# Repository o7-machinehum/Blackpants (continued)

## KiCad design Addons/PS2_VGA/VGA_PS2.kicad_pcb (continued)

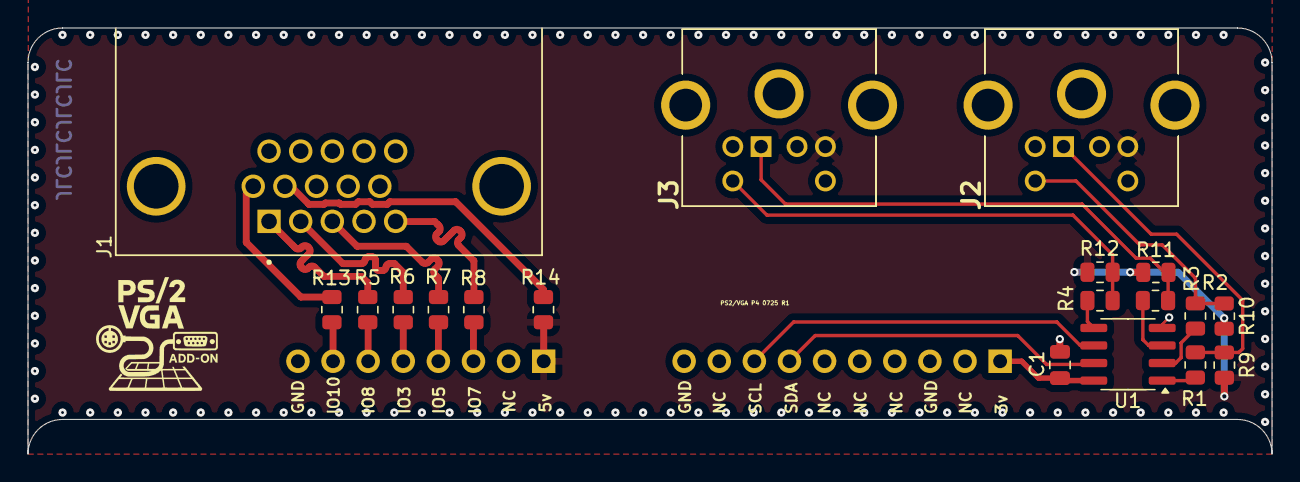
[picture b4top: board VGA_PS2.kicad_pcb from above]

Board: 2 copper layers, 90.0 x 30.8 mm, 21 parts (0 on the bottom side), 24 nets.

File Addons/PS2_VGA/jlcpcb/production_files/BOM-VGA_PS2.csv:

Comment,Designator,Footprint,LCSC,Quantity
220R,"R13,R8",R_0805_2012Metric,C114519,2
PCA9536D,U1,SOIC-8_3.9x4.9mm_P1.27mm,C129522,1
0R,,R_0805_2012Metric,C17477,0
330R,"R5,R6,R7",R_0805_2012Metric,C17630,3
200R,"R1,R2,R3,R4",R_0805_2012Metric,C2889551,4
5749266-1,"J2,J3",57492661,C3275792,2
100nF,C1,C_0805_2012Metric,C49678,1
L77HDE15SD1CH4FVGA,J1,AMPHENOL_L77HDE15SD1CH4FVGA,C5428609,1
10K,"R10,R11,R12,R9",R_0805_2012Metric,C84376,4
Conn_01x10_Pin,J4,PinHeader_1x10_P2.54mm_Horizontal,,1
Conn_01x08_Pin,J5,PinHeader_1x08_P2.54mm_Horizontal,,1

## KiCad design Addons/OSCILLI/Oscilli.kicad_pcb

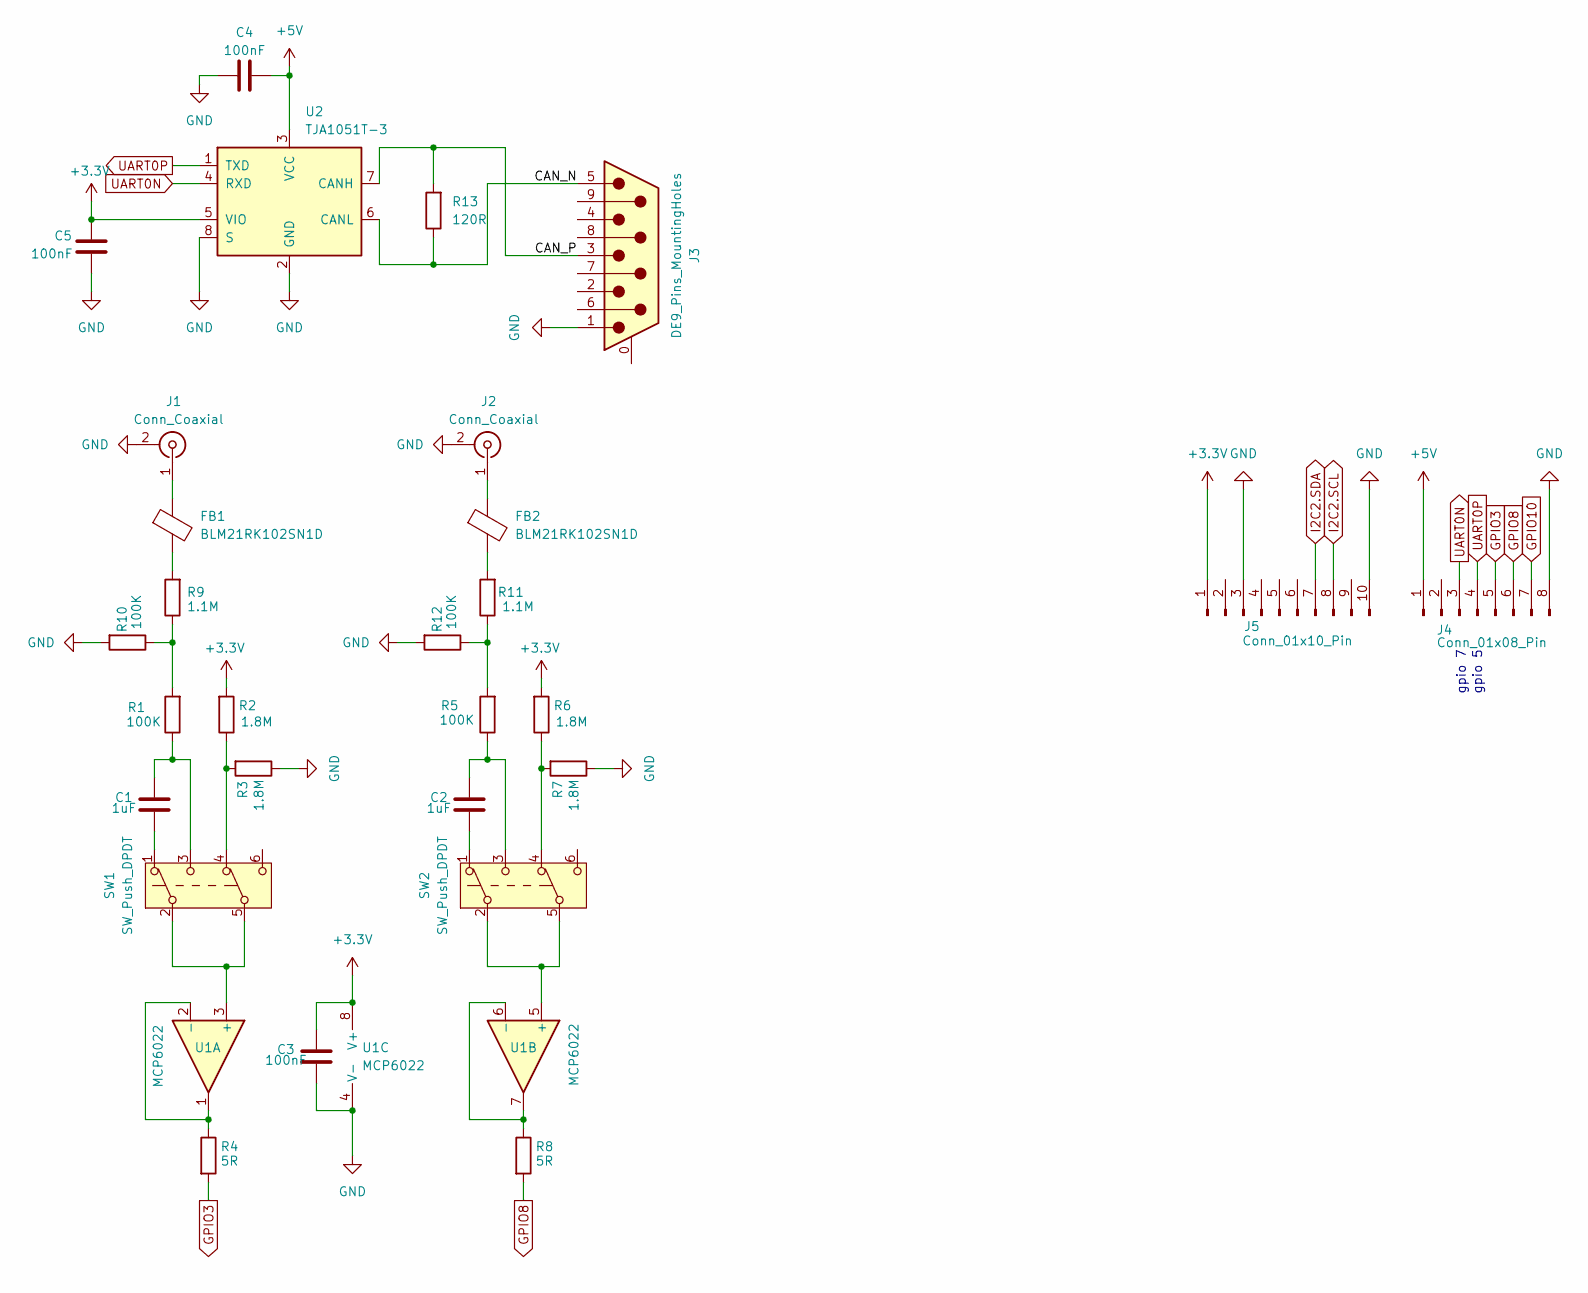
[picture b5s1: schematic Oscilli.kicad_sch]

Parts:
C1, C2: 1uF; C_0805_2012Metric
C3, C4, C5: 100nF; C_0805_2012Metric
FB1, FB2: BLM21RK102SN1D; L_0805_2012Metric
J1, J2: Conn_Coaxial; BNC_Amphenol_031-6575_Horizontal
J3: DE9_Pins_MountingHoles; DSUB-9_Socket_Horizontal_P2.77x2.84mm_EdgePinOffset4.94mm_H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
J4: Conn_01x08_Pin; PinHeader_1x08_P2.54mm_Horizontal
J5: Conn_01x10_Pin; PinHeader_1x10_P2.54mm_Horizontal
R1, R5, R10, R12: 100K; R_0805_2012Metric
R2, R3, R6, R7: 1.8M; R_0805_2012Metric
R4, R8: 5R; R_0805_2012Metric
R9, R11: 1.1M; R_0805_2012Metric
R13: 120R; R_0805_2012Metric
SW1, SW2: SW_Push_DPDT; SW_Push_2P2T_Toggle_CK_PVA2xxH4xxxxxxV2
U1: MCP6022; SOIC127P599X175-8N
U2: TJA1051T-3; SOIC-8_3.9x4.9mm_P1.27mm

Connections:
+3.3V: C3.2, C5.1, J5.1, R2.2, R6.2, U1.8 (V+), U2.5 (VIO)
+5V: C4.2, J4.1, U2.3 (VCC)
/CAN_N: J3.5, R13.1, U2.6 (CANL)
/CAN_P: J3.3, R13.2, U2.7 (CANH)
GND: C3.1, C4.1, C5.2, J1.2 (Ext), J2.2 (Ext), J3.1, J4.8, J5.3, J5.10, R3.1, R7.1, R10.2, R12.2, U1.4 (V-), U2.2 (GND), U2.8 (S)
GPIO3: J4.5, R4.2
GPIO8: J4.6, R8.2
GPIO10: J4.7
I2C2.SCL: J5.8
I2C2.SDA: J5.7
unnamed: C1.1, SW1.1 (A)
unnamed: C1.2, R1.1, SW1.3 (C)
unnamed: C2.1, SW2.1 (A)
unnamed: C2.2, R5.1, SW2.3 (C)
unnamed: FB1.2, R9.2
unnamed: FB2.2, R11.2
unnamed: FB1.1, J1.1 (In)
unnamed: FB2.1, J2.1 (In)
unnamed: R1.2, R9.1, R10.1
unnamed: R2.1, R3.2, SW1.4 (A)
unnamed: R6.1, R7.2, SW2.4 (A)
unnamed: R5.2, R11.1, R12.1
unnamed: SW1.2 (B), SW1.5 (B), U1.3 (+)
unnamed: R4.1, U1.1, U1.2 (-)
unnamed: SW2.2 (B), SW2.5 (B), U1.5 (+)
unnamed: R8.1, U1.6 (-), U1.7
UART0N: J4.3, U2.4 (RXD)
UART0P: J4.4, U2.1 (TXD)

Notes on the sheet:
gpio 7
gpio 5

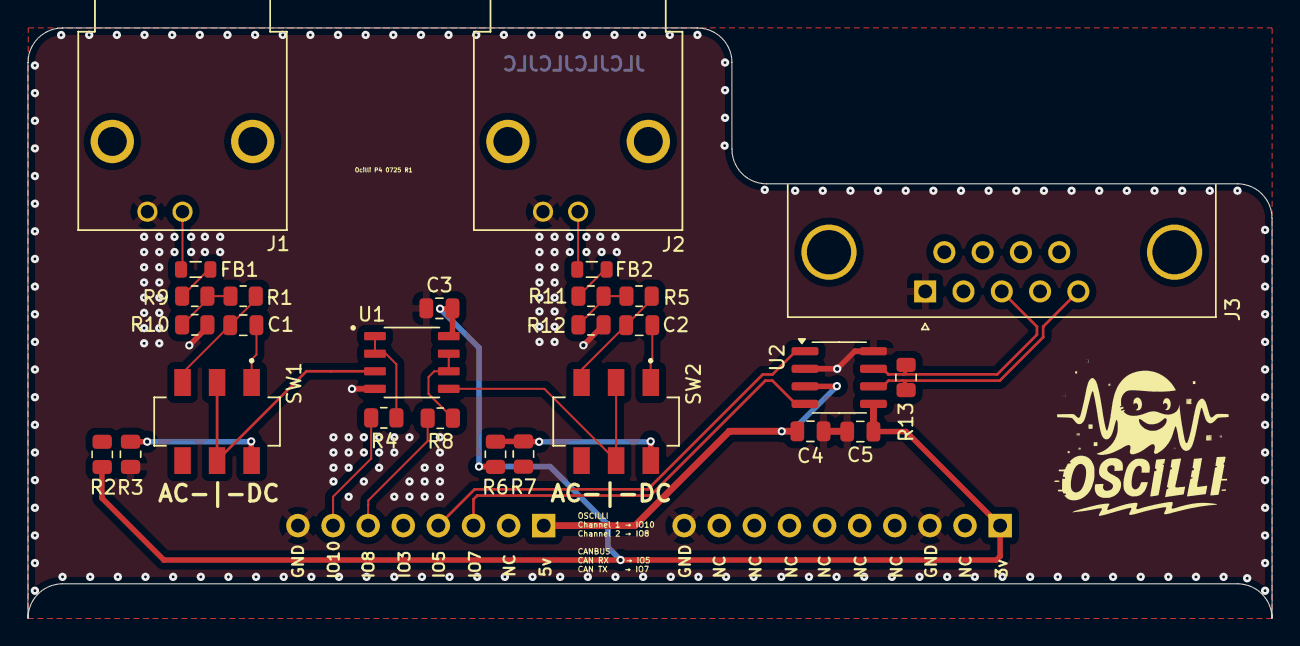
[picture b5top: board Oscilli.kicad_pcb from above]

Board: 2 copper layers, 90.0 x 42.7 mm, 29 parts (0 on the bottom side), 25 nets.

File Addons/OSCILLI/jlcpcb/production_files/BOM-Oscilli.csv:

Comment,Designator,Footprint,LCSC,Quantity
5R,"R4,R8",R_0805_2012Metric,C113035,2
100K,"R1,R10,R12,R5",R_0805_2012Metric,C149504,4
1.8M,"R2,R3,R6,R7",R_0805_2012Metric,C2930213,4
120R,R13,R_0805_2012Metric,C3013232,1
1.1M,"R11,R9",R_0805_2012Metric,C308358,2
1uF,"C1,C2",C_0805_2012Metric,C326587,2
TJA1051T-3,U2,SOIC-8_3.9x4.9mm_P1.27mm,C38695,1
100nF,"C3,C4,C5",C_0805_2012Metric,C49678,3
BLM21RK102SN1D,"FB1,FB2",L_0805_2012Metric,C498363,2
MCP6022,U1,SOIC127P599X175-8N,C57639,1
DE9_Pins_MountingHoles,J3,DSUB-9_Socket_Horizontal_P2.77x2.84mm_EdgePinOffset4.94mm_Housed_MountingHolesOffset4.94mm,,1
SW_Push_DPDT,SW2,SW_SLW-913535-2A-SMT,,1
Conn_01x10_Pin,J5,PinHeader_1x10_P2.54mm_Horizontal,,1
Conn_01x08_Pin,J4,PinHeader_1x08_P2.54mm_Horizontal,,1
Conn_Coaxial,J2,TE_5415218-5,,1
Conn_Coaxial,J1,TE_5415218-5,,1
SW_Push_DPDT,SW1,SW_SLW-913535-2A-SMT,,1

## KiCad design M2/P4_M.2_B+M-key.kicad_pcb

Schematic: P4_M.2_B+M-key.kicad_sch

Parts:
C2, C3, C4, C5, C6, C7, C9, C10, C11, C12, C14, C15, C16, C17, C18, C19, C20, C22, C23, C24, C25, C26, C27, C32, C38, C48, C50: 100nF; C_0201_0603Metric; LCSC C301918
C13, C21, C28, C29: 22pF; C_0201_0603Metric; LCSC C57783
C33, C34, C46, C47: 22uF; C_0603_1608Metric; LCSC C86295
C37, C49: 10uF; C_0603_1608Metric; LCSC C6119842
D1: LED; LED_0402_1005Metric; LCSC C22355736
D2: K24; D_SOD-123F; LCSC C5199107
D3: RED; LED_0603_1608Metric; LCSC C965799
IC1: XT25F128FWOIGT-W; WSON-8-1EP_6x5mm_P1.27mm_EP3.4x4mm; LCSC C3202839
IC2, IC4: TPS563202DRLR; SOT-563; LCSC C1513007
J1: Micro_SD_Card_Det2; uSD_CARD; LCSC C2962030
J2: USB_C_Receptacle_USB2.0_16P; USB_C_Receptacle_HRO_TYPE-C-31-M-22; LCSC C530612; not fitted
L1: VLS4012HBX-3R3M-N; IND_VLS4012HBX-3R3M-N; LCSC C3223566
L2: FTC252012S1R5MBCA; L_Changjiang_FNR252010S; LCSC C5832371
Q2: MMDT2222A; SOT-363_SC-70-6; LCSC C7603394
R1, R2: 5.1k; R_0201_0603Metric; LCSC C270344
R3, R4, R6, R7, R8, R24, R26, R30, R31: 10k; R_0201_0603Metric; LCSC C473048
R5: 4.7k; R_0201_0603Metric; LCSC C270346
R9: 220R; R_0201_0603Metric; LCSC C965330
R10, R11, R12, R13, R14: 51K; R_0201_0603Metric; LCSC C473471
R15: 1k; R_0201_0603Metric; LCSC C270365
R16, R23: 0; R_0201_0603Metric; LCSC C106228
R18: 47R; R_0201_0603Metric; LCSC C620443
R19: 100K; R_0201_0603Metric; LCSC C270364
R22: 31k; R_0201_0603Metric; LCSC C364366
R25: 4.9K; R_0201_0603Metric; LCSC C367640
R27: 150R; R_0201_0603Metric; LCSC C270329
R28, R29: 4.02k; R_0201_0603Metric; LCSC C270347
U2: ESP32-P4NRW16; IC_ESP32-P4NRW16; LCSC C22387510
U4: M.2-M-KEY
U5: CH340K; SSOP-10-1EP_3.9x4.9mm_P1mm_EP2.1x3.3mm; LCSC C968586
Y1: 32KHz; Crystal_SMD_3215-2Pin_3.2x1.5mm; LCSC C5361379
Y2: 40MHz; Crystal_SMD_2016-4Pin_2.0x1.6mm; LCSC C20885029

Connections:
/1.2V: C7.2, C20.2, C26.2, C33.1, C34.1, L2.1, R25.2, U2.26 (VDD_HP_0), U2.76 (VDD_HP_2), U2.91 (VDD_HP_3)
/3.3V: C2.2, C3.2, C5.2, C9.2, C10.2, C12.2, C14.2, C19.2, C22.2, C24.2, C25.2, C46.1, C47.1, C50.2, L1.1, R4.1, R5.1, R6.1, R7.1, R8.2, R15.1, R16.2, R22.2, U2.9 (VDDPST_1), U2.21 (VDDPST_2), U2.30 (VDDPST_3), U2.51 (VCCA), U2.59 (VDDPST), U2.62 (VDDPST_4), U2.67 (VDDPST), U2.75 (VDDPST_LDO), U2.77 (VDDPST_DCDC), U2.96 (VDDPST_6), U2.101 (VDDA), U4.68, U4.70, U4.72, U4.74, U5.7 (VCC), U5.10 (V3)
/CSI_CLKN: U2.45 (CSI_CLKN), U4.15
/CSI_CLKP: U2.44 (CSI_CLKP), U4.17
/CSI_DATAN0: U2.42 (CSI_DATAN0), U4.23
/CSI_DATAN1: U2.46 (CSI_DATAN1), U4.11
/CSI_DATAP0: U2.43 (CSI_DATAP0), U4.21
/CSI_DATAP1: U2.47 (CSI_DATAP1), U4.9
/CSI_REXT: R28.1, U2.48 (CSI_REXT)
/DSI_CLKN: U2.37 (DSI_CLKN), U4.35
/DSI_CLKP: U2.38 (DSI_CLKP), U4.33
/DSI_DATAN0: U2.40 (DSI_DATAN0), U4.27
/DSI_DATAN1: U2.36 (DSI_DATAN1), U4.39
/DSI_DATAP0: U2.39 (DSI_DATAP0), U4.29
/DSI_DATAP1: U2.35 (DSI_DATAP1), U4.41
/DSI_REXT: R29.1, U2.34 (DSI_REXT)
/DTR: Q2.1 (E1), R31.1, U5.4 (~DTR)
/EN_DCDC: IC2.5 (EN), U2.79 (EN_DCDC)
/EN_ESP: C6.2, Q2.3 (C2), R4.2, U2.103 (CHIP_PU)
/FB: IC4.6 (FB), R22.1, R24.2
/FB2: IC2.6 (FB), R23.1, R25.1, R26.2
/FLASH_CK: IC1.6 (SCLK), U2.32 (FLASH_CK)
/FLASH_CS: IC1.1 (CS#), R3.1, U2.27 (FLASH_CS)
/FLASH_D: IC1.5 (SI_(IO0)), U2.33 (FLASH_D)
/FLASH_HOLD: IC1.7 (HOLD#/_RESET#_(IO3)), U2.31 (FLASH_HOLD)
/FLASH_Q: IC1.2 (SO_(IO1)), U2.28 (FLASH_Q)
/FLASH_WP: IC1.3 (WP#_(IO2)), U2.29 (FLASH_WP)
/GPIO2: U2.2 (GPIO2), U4.22
/GPIO3: U2.3 (GPIO3), U4.58
/GPIO4: U2.4 (GPIO4), U4.24
/GPIO5: U2.5 (GPIO5), U4.56
/GPIO6: U2.6 (GPIO6), U4.26
/GPIO7: U2.7 (GPIO7), U4.54
/GPIO8: U2.8 (GPIO8), U4.28
/GPIO9: U2.10 (GPIO9), U4.52
/GPIO10: U2.11 (GPIO10), U4.30
/GPIO11: U2.12 (GPIO11)
/GPIO12: U2.13 (GPIO12), U4.32
/GPIO13: U2.14 (GPIO13), U4.34
/GPIO14: U2.15 (GPIO14), U4.36
/GPIO15: U2.16 (GPIO15), U4.38
/GPIO16: U2.17 (GPIO16), U4.40
/GPIO17: U2.18 (GPIO17), U4.42
/GPIO18: U2.19 (GPIO18), U4.46
/GPIO19: U2.20 (GPIO19), U4.44
/GPIO20: U2.22 (GPIO20), U4.48
/GPIO21: U2.23 (GPIO21)
/GPIO22: U2.24 (GPIO22), U4.50
/GPIO35: C11.2, Q2.6 (C1), R5.2, U2.66 (GPIO35)
/GPIO37: R6.2, U2.69 (GPIO37), U5.9 (RXD)
/GPIO38: R7.2, U2.70 (GPIO38), U5.8 (TXD)
/I2S_DATA: U2.52 (GPIO24), U4.2
/I2S_LRCK: U2.56 (GPIO27), U4.4
/I2S_MCLK: U2.55 (GPIO26), U4.6
/I2S_SCLK: U2.53 (GPIO25), U4.8
/REST_N: U2.92 (GPIO49)
/RTC: C23.2, R16.1, U2.102 (VBAT), U4.67
/RTS: Q2.4 (E2), R15.2, R30.1, U5.6 (~RTS)
/SD2_CLK: U2.63 (GPIO32), U4.18
/SD2_CMD: U2.64 (GPIO33), U4.20
/SD2_DATA0: U2.57 (GPIO28), U4.10
/SD2_DATA1: U2.61 (GPIO31), U4.12
/SD2_DATA2: U2.60 (GPIO30), U4.14
/SD2_DATA3: U2.58 (GPIO29), U4.16
/SD_CLK: R18.1, U2.84 (GPIO43)
/SD_CMD: J1.3 (CMD), R19.2, U2.86 (GPIO44)
/SD_DATA0: J1.7 (DAT0), R10.2, U2.80 (GPIO39)
/SD_DATA1: J1.8 (DAT1), R11.2, U2.81 (GPIO40)
/SD_DATA2: J1.1 (DAT2), R12.2, U2.82 (GPIO41)
/SD_DATA3: J1.2 (DAT3/CD), R13.2, U2.83 (GPIO42)
/SD_DET: J1.9 (DET_B), U2.88 (GPIO46)
/USB2HS_D+: U2.50 (DP), U4.3
/USB2HS_D-: U2.49 (DM), U4.5
/USB5V: C37.1, C49.1, D2.1 (K), IC2.1 (VIN), IC4.1 (VIN), IC4.5 (EN), R9.2, U4.69, U4.71, U4.73, U4.75
/USBJTAG_D+: J2.A6 (D+), J2.B6 (D+), U4.45, U5.1 (UD+)
/USBJTAG_D-: J2.A7 (D-), J2.B7 (D-), U4.47, U5.2 (UD-)
/VFLASH: C15.2, IC1.8 (VCC), R3.2, U2.71 (VFB1/VO1)
/VMIPI: C4.2, C17.2, U2.41 (VDD_MIPI_DPHY), U2.73 (VFB3/VO3)
/VPSRAM: C16.2, U2.72 (VFB2/VO2)
/V/SDMMC: C18.2, C27.2, C38.1, J1.4 (VDD), R10.1, R11.1, R12.1, R13.1, R14.1, R19.1, U2.74 (VFB4/VO4), U2.85 (VDDPST_5)
GND: C2.1, C3.1, C4.1, C5.1, C6.1, C7.1, C9.1, C10.1, C11.1, C12.1, C13.1, C14.1, C15.1, C16.1, C17.1, C18.1, C19.1, C20.1, C21.1, C22.1, C23.1, C24.1, C25.1, C26.1, C27.1, C28.2, C29.2, C33.2, C34.2, C37.2, C38.2, C46.2, C47.2, C49.2, C50.1, D1.1 (K), D3.1 (K), IC1.4 (VSS), IC1.9 (EP), IC2.3 (GND), IC4.3 (GND), J1.6 (VSS), J1.11 (SHIELD), J2.A1 (GND), J2.A12 (GND), J2.B1 (GND), J2.B12 (GND), J2.S1 (SHIELD), R1.2, R2.2, R24.1, R26.1, R28.2, R29.2, U2.105 (GND), U4.1, U4.7, U4.13, U4.19, U4.25, U4.31, U4.37, U4.43, U4.49, U4.MP (screw), U5.3 (GND), U5.11 (GND), Y2.2, Y2.4
unnamed: D1.2 (A), R27.2
unnamed: D2.2 (A), J2.A4 (VBUS), J2.A9 (VBUS), J2.B4 (VBUS), J2.B9 (VBUS)
unnamed: D3.2 (A), R9.1
unnamed: C32.2, IC2.4 (BST)
unnamed: C32.1, IC2.2 (SW), L2.2
unnamed: C48.2, IC4.4 (BST)
unnamed: C48.1, IC4.2 (SW), L1.2
unnamed: J1.5 (CLK), R18.2
unnamed: J1.10 (DET_A), R14.2
unnamed: J2.A5 (CC1), R1.1
unnamed: J2.B5 (CC2), R2.1
unnamed: Q2.2 (B1), R30.2
unnamed: Q2.5 (B2), R31.2
unnamed: R23.2, U2.78 (FB_DCDC)
unnamed: C21.2, U2.104 (GPIO0), Y1.2
unnamed: C13.2, U2.1 (GPIO1), Y1.1
unnamed: R8.1, U2.68 (GPIO36)
unnamed: R27.1, U2.94 (GPIO51)
unnamed: C29.1, U2.99 (XTAL_N), Y2.3
unnamed: C28.1, U2.100 (XTAL_P), Y2.1

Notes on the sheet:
40Mhz
UART / AUTO FLASHER
32Mhz
M.2 B+M KEY
FLASH
PD MAIN
1.8v 0.1A OUTPUT
2.5v 0.1A OUTPUT
POWER
1.8v / 3.3v 0.2A OUTPUT (SDIO)
ESP-P4

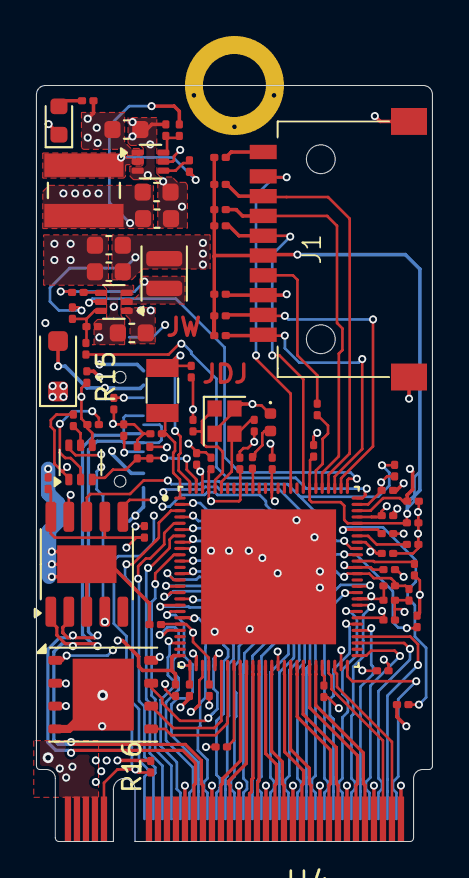
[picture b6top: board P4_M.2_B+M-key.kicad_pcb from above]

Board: 4 copper layers, 22.0 x 42.0 mm, 81 parts (1 on the bottom side), 98 nets.

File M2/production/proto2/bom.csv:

Comment,Designator,Footprint,LCSC
22pF,"C13,C21,C28,C29",Capacitor_SMD:C_0201_0603Metric,C57783
51K,"R10,R11,R12,R13,R14",Resistor_SMD:R_0201_0603Metric,C473471
RED,D3,LED_SMD:LED_0603_1608Metric,C965799
100nF,"C2,C3,C4,C5,C6,C7,C9,C10,C11,C12,C14,C15,C16,C17,C18,C19,C20,C22,C23,C24,C25,C26,C27,C32,C38,C48,C50",Capacitor_SMD:C_0201_0603Metric,C301918
4.02k,"R28,R29",Resistor_SMD:R_0201_0603Metric,C270347
MMDT2222A,Q2,Package_TO_SOT_SMD:SOT-363_SC-70-6,C7603394
4.7k,R5,Resistor_SMD:R_0201_0603Metric,C270346
ESP32-P4NRW16,U2,P4_M.2_B+M-key:IC_ESP32-P4NRW16,C22387510
10k,"R3,R4,R6,R7,R8,R24,R26,R30,R31",Resistor_SMD:R_0201_0603Metric,C473048
4.9K,R25,Resistor_SMD:R_0201_0603Metric,C367640
40MHz,Y2,Crystal:Crystal_SMD_2016-4Pin_2.0x1.6mm,C20885029
100K,R19,Resistor_SMD:R_0201_0603Metric,C270364
LED,D1,LED_SMD:LED_0402_1005Metric,C22355736
22uF,"C33,C34,C46,C47",Capacitor_SMD:C_0603_1608Metric,C86295
10uF,"C37,C49",Capacitor_SMD:C_0603_1608Metric,C6119842
TPS563202DRLR,"IC2,IC4",Package_TO_SOT_SMD:SOT-563,C1513007
5.1k,"R1,R2",Resistor_SMD:R_0201_0603Metric,C270344
XT25F128FWOIGT-W,IC1,Package_SON:WSON-8-1EP_6x5mm_P1.27mm_EP3.4x4mm,C3202839
K24,D2,Diode_SMD:D_SOD-123F,C5199107
31k,R22,Resistor_SMD:R_0201_0603Metric,C364366
32KHz,Y1,Crystal:Crystal_SMD_3215-2Pin_3.2x1.5mm,C5361379
0,R23,Resistor_SMD:R_0201_0603Metric,C106228
Micro_SD_Card_Det2,J1,WHY:uSD_CARD,C2962030
47R,R18,Resistor_SMD:R_0201_0603Metric,C620443
FTC252012S1R5MBCA,L2,Inductor_SMD:L_Changjiang_FNR252010S,C5832371
VLS4012HBX-3R3M-N,L1,P4_M.2_B+M-key:IND_VLS4012HBX-3R3M-N,C3223566
CH340K,U5,Package_SO:SSOP-10-1EP_3.9x4.9mm_P1mm_EP2.1x3.3mm,C968586
150R,R27,Resistor_SMD:R_0201_0603Metric,C270329
220R,R9,Resistor_SMD:R_0201_0603Metric,C965330

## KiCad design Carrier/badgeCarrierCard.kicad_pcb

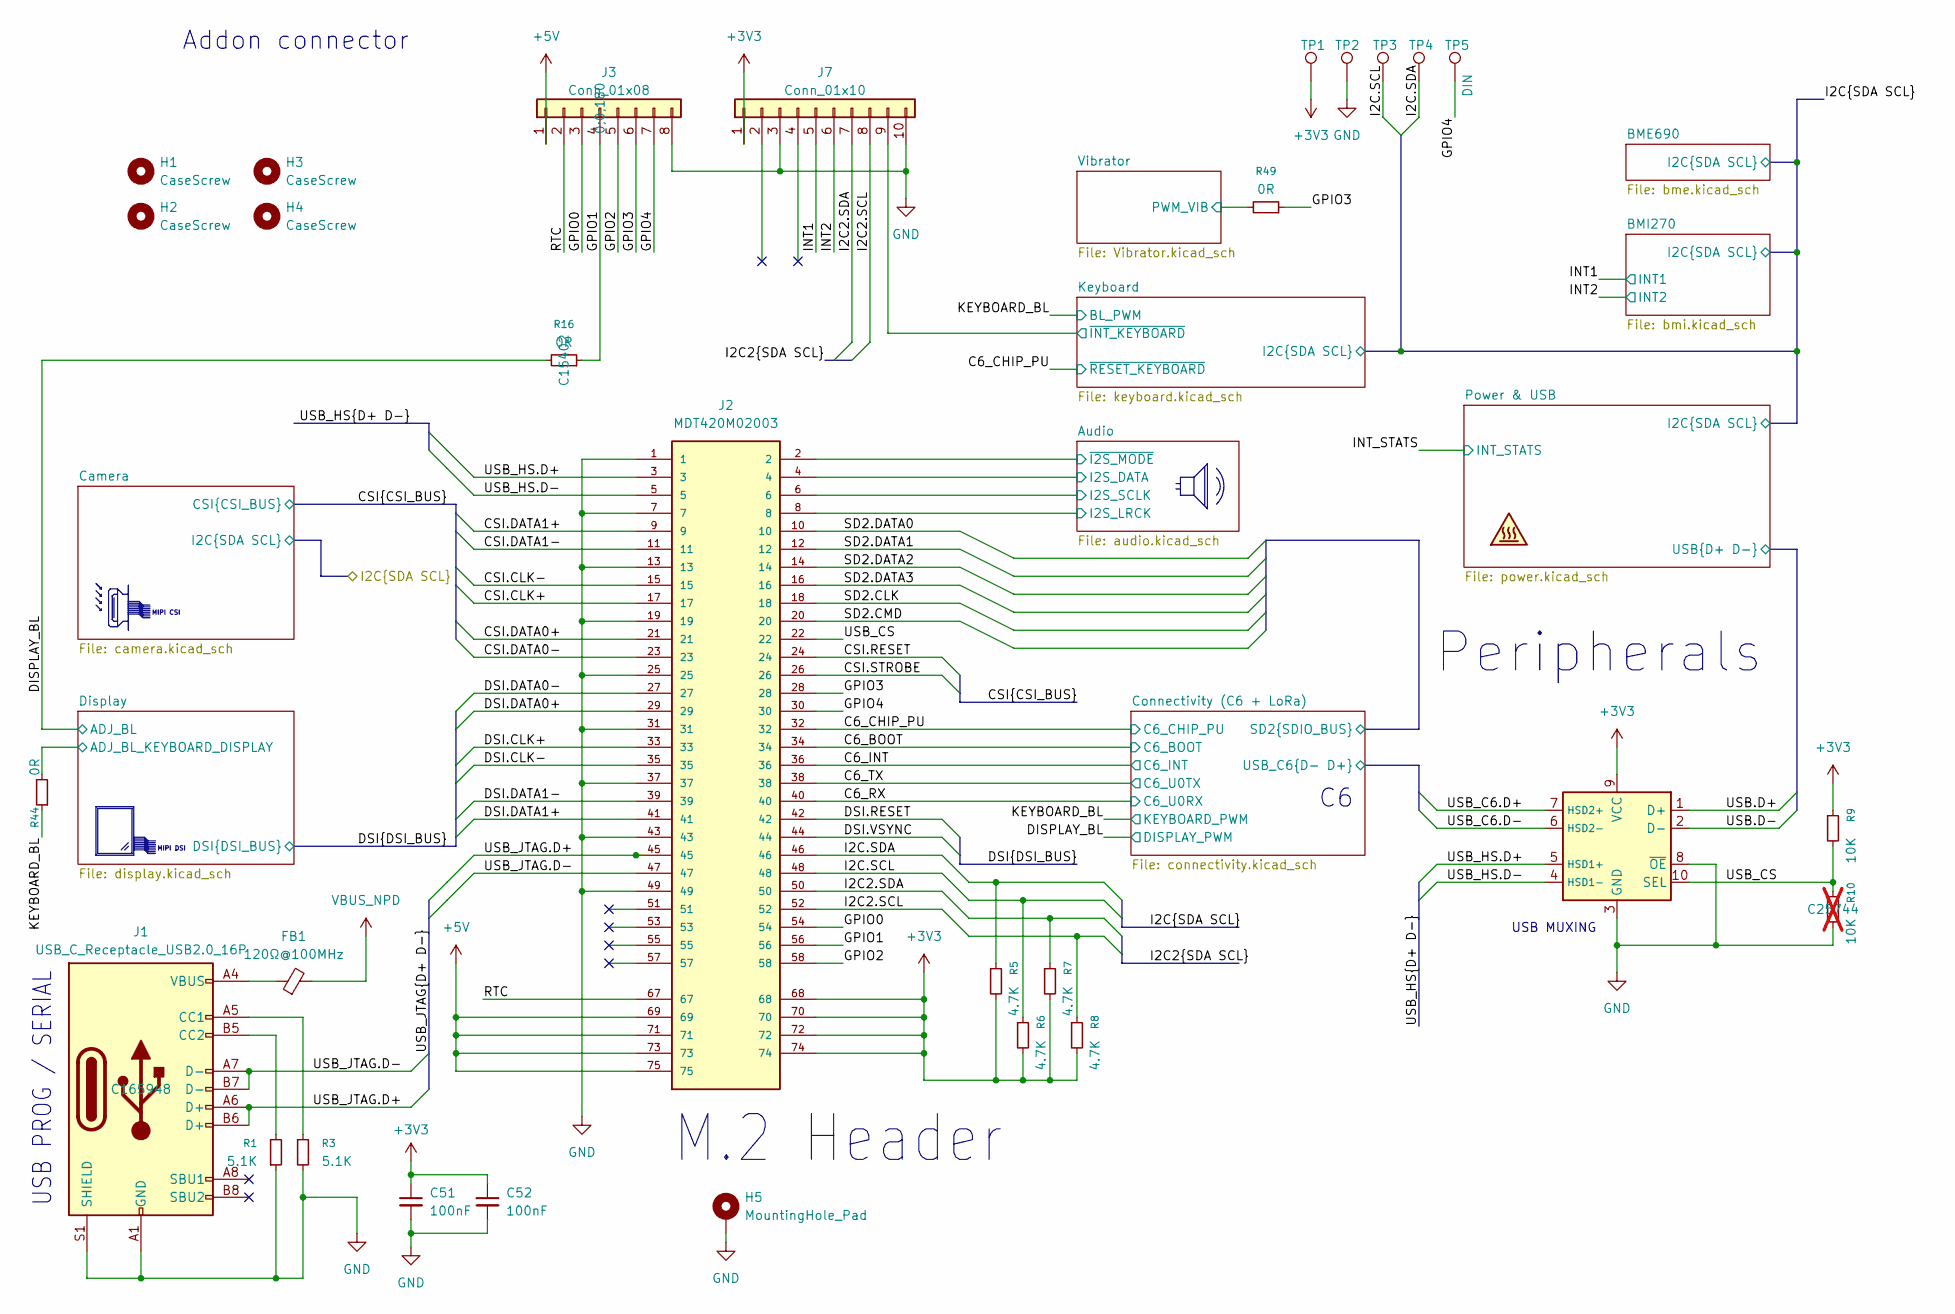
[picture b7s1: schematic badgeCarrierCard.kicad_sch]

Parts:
C51, C52: 100nF; C_0402_1005Metric; LCSC C307331
FB1: 120Ω@100MHz; L_0402_1005Metric; LCSC C76891
H1, H2, H3, H4: CaseScrew; MountingHole_2.2mm_M2
H5: MountingHole_Pad; Standoff; LCSC C19626599
J1: USB_C_Receptacle_USB2.0_16P; USB_C_Receptacle_HRO_TYPE-C-31-M-12; LCSC C165948
J2: MDT420M02003; AMPHENOL_MDT420M02003; PARTREV 1; LCSC C410529
J3: Conn_01x08; SMD_8; LCSC C5142241
J7: Conn_01x10; SMD_10; LCSC C5142243
R1, R3: 5.1K; R_0402_1005Metric; LCSC C25905
R5, R6, R7, R8: 4.7K; R_0402_1005Metric; LCSC C25900
R9: 10K; R_0402_1005Metric; LCSC C25744
R10: 10K; R_0402_1005Metric; LCSC C25744; not fitted
R16, R44: 0R; R_0603_1608Metric; LCSC C15402
R49: 0R; R_0402_1005Metric; LCSC C15402
TP1, TP2, TP3, TP4: TestPoint; TestPoint_Pad_D1.0mm
TP5: DIN; TestPoint_Pad_D1.0mm
U11: TPSGM7227YUWQ10G; UQFN-10_1.4x1.8mm_P0.4mm; LCSC C42379165

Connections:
/Audio/I2S_DATA: J2.4; also elsewhere on the board
/Audio/I2S_LRCK: J2.8; also elsewhere on the board
/Audio/I2S_SCLK: J2.6; also elsewhere on the board
/Audio/~I2S_MODE: J2.2; also elsewhere on the board
/C6_BOOT: J2.34; also elsewhere on the board
/C6_CHIP_PU: J2.32; also elsewhere on the board
/C6_INT: J2.36; also elsewhere on the board
/C6_RX: J2.40; also elsewhere on the board
/C6_TX: J2.38; also elsewhere on the board
/CSI.CLK+: J2.17; also elsewhere on the board
/CSI.CLK-: J2.15; also elsewhere on the board
/CSI.DATA0+: J2.21; also elsewhere on the board
/CSI.DATA0-: J2.23; also elsewhere on the board
/CSI.DATA1+: J2.9; also elsewhere on the board
/CSI.DATA1-: J2.11; also elsewhere on the board
/CSI.RESET: J2.24; also elsewhere on the board
/CSI.STROBE: J2.26; also elsewhere on the board
/Connectivity (C6 + LoRa)/SD2.CLK: J2.18; also elsewhere on the board
/Connectivity (C6 + LoRa)/SD2.CMD: J2.20; also elsewhere on the board
/Connectivity (C6 + LoRa)/SD2.DATA0: J2.10; also elsewhere on the board
/Connectivity (C6 + LoRa)/SD2.DATA1: J2.12; also elsewhere on the board
/Connectivity (C6 + LoRa)/SD2.DATA2: J2.14; also elsewhere on the board
/Connectivity (C6 + LoRa)/SD2.DATA3: J2.16; also elsewhere on the board
/Connectivity (C6 + LoRa)/USB_C6.D+: U11.7 (HSD2+); also elsewhere on the board
/Connectivity (C6 + LoRa)/USB_C6.D-: U11.6 (HSD2-); also elsewhere on the board
/DISPLAY_BL: R16.2; also elsewhere on the board
/DSI.CLK+: J2.33; also elsewhere on the board
/DSI.CLK-: J2.35; also elsewhere on the board
/DSI.DATA0+: J2.29; also elsewhere on the board
/DSI.DATA0-: J2.27; also elsewhere on the board
/DSI.DATA1+: J2.41; also elsewhere on the board
/DSI.DATA1-: J2.39; also elsewhere on the board
/DSI.RESET: J2.42; also elsewhere on the board
/DSI.VSYNC: J2.44
/Display/ADJ_BL_KEYBOARD_DISPLAY: R44.2; also elsewhere on the board
/GPIO0: J2.54, J3.3
/GPIO1: J2.56, J3.4, R16.1
/GPIO2: J2.58, J3.5
/GPIO3: J2.28, J3.6, R49.1
/GPIO4: J2.30, J3.7, TP5.1
/I2C2.SCL: J2.52, J7.8, R8.1
/I2C2.SDA: J2.50, J7.7, R7.1
/I2C.SCL: J2.48, R6.1, TP3.1; also elsewhere on the board
/I2C.SDA: J2.46, R5.1, TP4.1; also elsewhere on the board
/INT1: J7.5; also elsewhere on the board
/INT2: J7.6; also elsewhere on the board
/KEYBOARD_BL: R44.1; also elsewhere on the board
/Keyboard/~INT_KEYBOARD: J7.9; also elsewhere on the board
/Power & USB/USB.D+: U11.1 (D+); also elsewhere on the board
/Power & USB/USB.D-: U11.2 (D-); also elsewhere on the board
/RTC: J2.67, J3.2
/USB_CS: J2.22, R9.2, R10.1, U11.10 (SEL)
/USB_HS.D+: J2.3, U11.5 (HSD1+)
/USB_HS.D-: J2.5, U11.4 (HSD1-)
/USB_JTAG.D+: J1.A6 (D+), J1.B6 (D+), J2.45
/USB_JTAG.D-: J1.A7 (D-), J1.B7 (D-), J2.47
unnamed: FB1.1, J1.A4 (VBUS), J1.A9 (VBUS), J1.B4 (VBUS), J1.B9 (VBUS)
unnamed: J1.A5 (CC1), R3.1
unnamed: J1.B5 (CC2), R1.2
VBUS_NPD: FB1.2; also elsewhere on the board

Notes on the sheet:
M.2 Header
MIPI CSI
Peripherals
USB MUXING
USB PROG / SERIAL
MIPI DSI
Addon connector

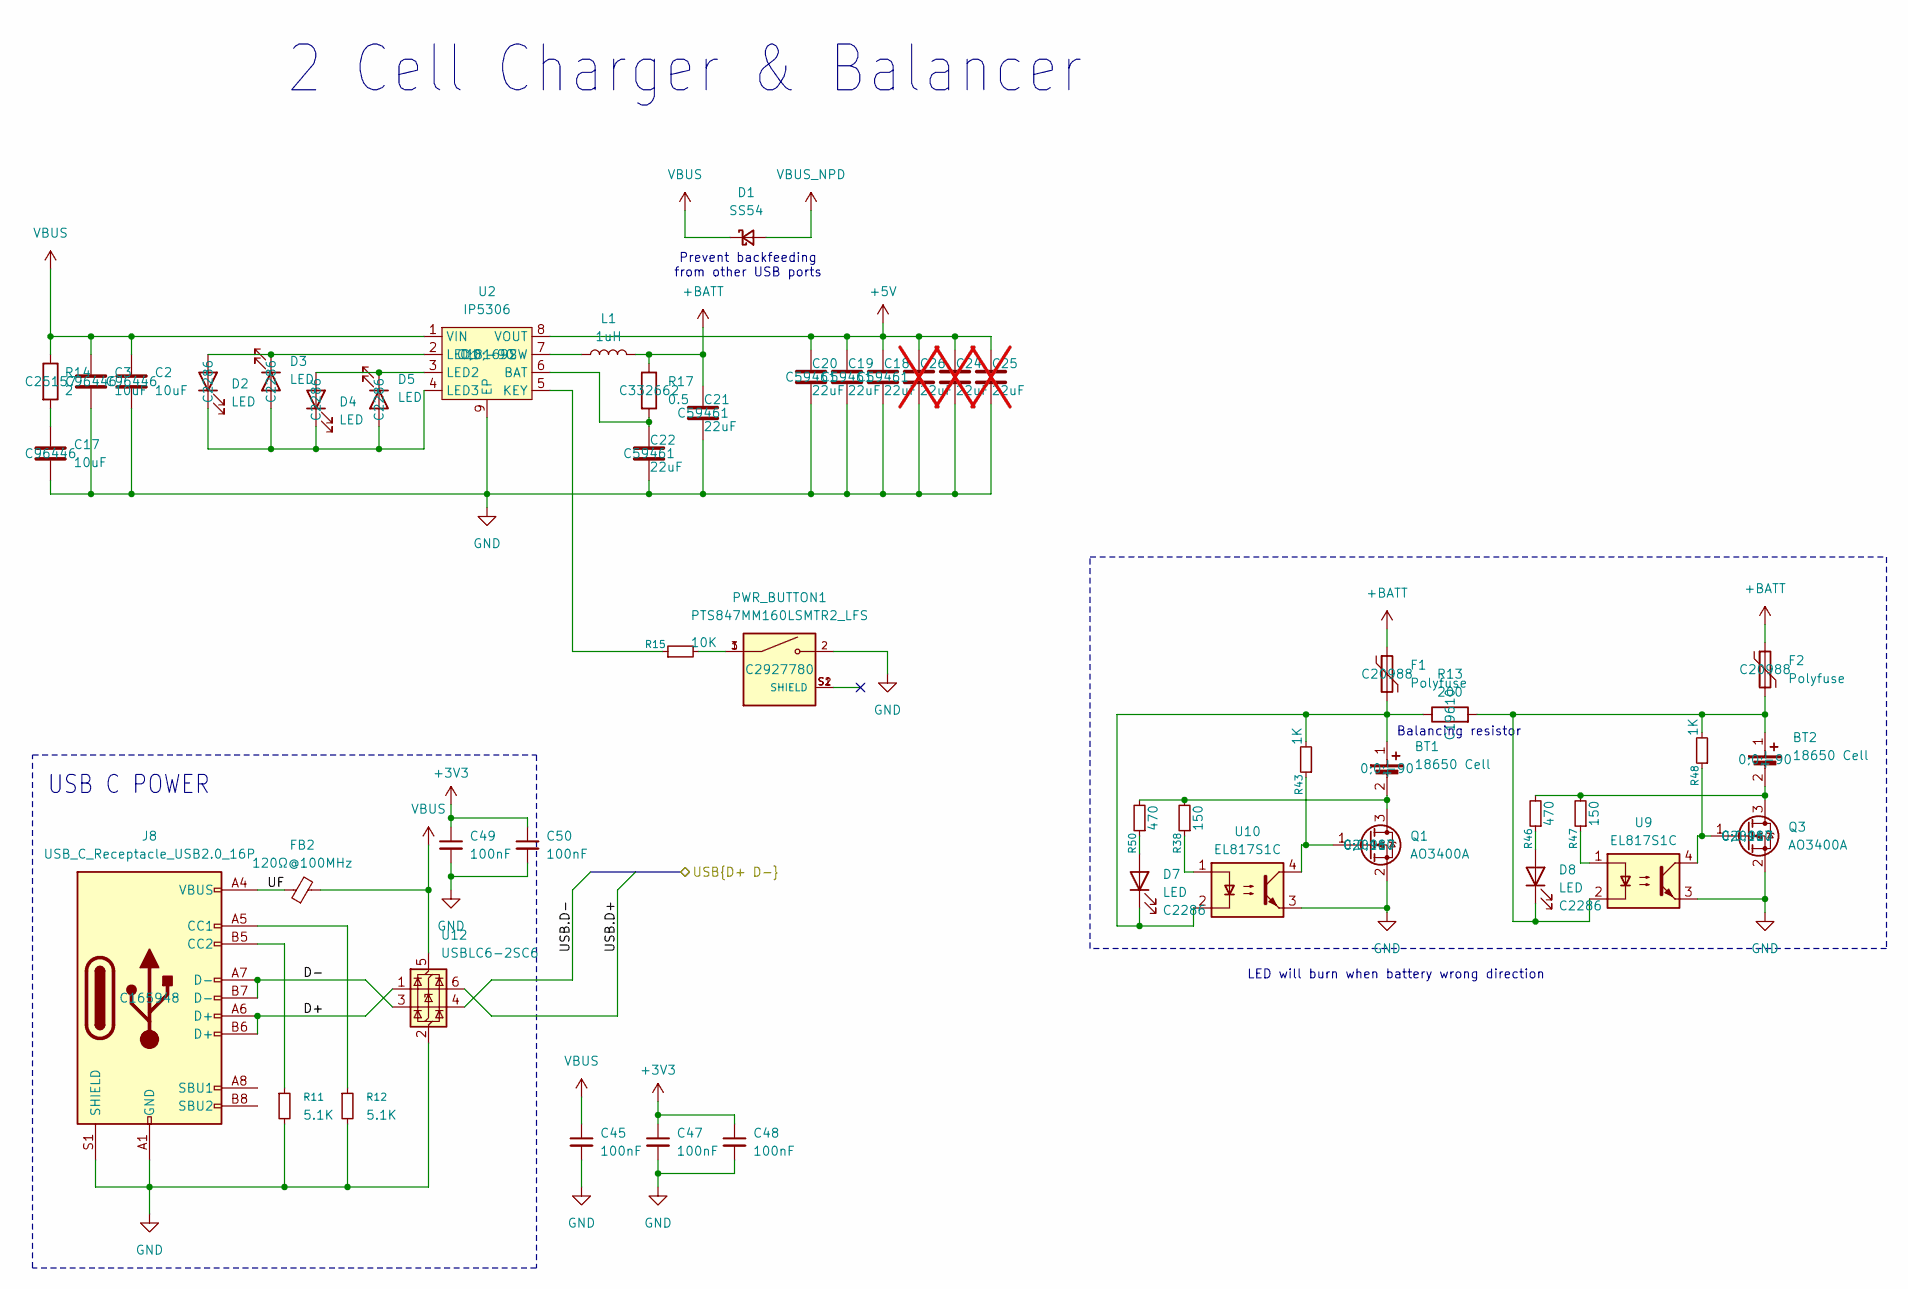
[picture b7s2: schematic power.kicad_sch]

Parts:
BT1, BT2: 18650 Cell; BH-18650-B1BA002; LCSC C2988620
C2, C3, C17: 10uF; C_0603_1608Metric; LCSC C96446
C18, C19, C20, C21, C22: 22uF; C_0603_1608Metric; LCSC C59461
C24, C25, C26: 22uF; C_0603_1608Metric; LCSC C59461; not fitted
C45, C47, C48, C49, C50: 100nF; C_0402_1005Metric; LCSC C307331
D1: SS54; D_SMA; LCSC C22452
D2, D3, D4, D5: LED; D_0603_1608Metric; LCSC C2286
D7, D8: LED; LED_0603_1608Metric; LCSC C2286
F1, F2: Polyfuse; Fuse_1206_3216Metric; LCSC C20988
FB2: 120Ω@100MHz; L_0402_1005Metric; LCSC C76891
J8: USB_C_Receptacle_USB2.0_16P; USB_C_Receptacle_HRO_TYPE-C-31-M-12; LCSC C165948
L1: 1uH; L_Changjiang_FXL0420; LCSC C32712969
PWR_BUTTON1: PTS847MM160LSMTR2_LFS; SW_PTS847MM160LSMTR2_LFS; PARTREV B; LCSC C2927780
Q1, Q3: AO3400A; SOT-23; LCSC C20917
R11, R12: 5.1K; R_0402_1005Metric; LCSC C25905
R13: 200; R_2010_5025Metric; LCSC C19610
R14: 2; R_0402_1005Metric; LCSC C25157
R15: 10K; R_0402_1005Metric; LCSC C25744
R17: 0.5; R_0402_1005Metric; LCSC C332662
R38, R47: 150; R_0402_1005Metric; LCSC C25082
R43, R48: 1K; R_0402_1005Metric; LCSC C11702
R46, R50: 470; R_0402_1005Metric; LCSC C25117
U2: IP5306; HSOP-8-1EP_3.9x4.9mm_P1.27mm_EP2.41x3.1mm_ThermalVias; LCSC C181692
U9, U10: EL817S1C; SOIC254P1030X390-4N; LCSC C2912100
U12: USBLC6-2SC6; SOT-23-6; LCSC C7519

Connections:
+BATT: C21.1, F1.1, F2.1, L1.2, R17.1
/Power & USB/D+: J8.A6 (D+), J8.B6 (D+), U12.1 (I/O1)
/Power & USB/D-: J8.A7 (D-), J8.B7 (D-), U12.3 (I/O2)
/Power & USB/UF: FB2.1, J8.A4 (VBUS), J8.A9 (VBUS), J8.B4 (VBUS), J8.B9 (VBUS)
/Power & USB/USB.D+: U12.6 (I/O1); also elsewhere on the board
/Power & USB/USB.D-: U12.4 (I/O2); also elsewhere on the board
unnamed 92: BT1.1 (+), D7.1 (K), F1.2, R13.1, R43.2, U10.2; also elsewhere on the board
unnamed 93: BT1.2 (-), Q1.3 (D), R38.2, R50.2; also elsewhere on the board
unnamed: BT2.1 (+), D8.1 (K), F2.2, R13.2, R48.2, U9.2
unnamed: BT2.2 (-), Q3.3 (D), R46.2, R47.2
unnamed: C17.1, R14.2
unnamed: D2.2 (A), D3.1 (K), U2.2 (LED1)
unnamed: D2.1 (K), D3.2 (A), D4.1 (K), D5.2 (A), U2.4 (LED3)
unnamed: D4.2 (A), D5.1 (K), U2.3 (LED2)
unnamed: D8.2 (A), R46.1
unnamed: J8.A5 (CC1), R12.1
unnamed: J8.B5 (CC2), R11.1
unnamed: PWR_BUTTON1.1, PWR_BUTTON1.3, R15.2
unnamed 119: Q1.1 (G), R43.1, U10.4; also elsewhere on the board
unnamed: Q3.1 (G), R48.1, U9.4
unnamed 122: R38.1, U10.1; also elsewhere on the board
unnamed: R47.1, U9.1
unnamed: C22.1, R17.2, U2.6 (BAT)
unnamed: R15.1, U2.5 (KEY)
unnamed: L1.1, U2.7 (SW)
VBUS: C2.1, C3.1, C45.1, D1.1 (K), FB2.2, R14.1, U2.1 (VIN), U12.5 (VBUS)
VBUS_NPD: D1.2 (A); also elsewhere on the board

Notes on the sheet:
2 Cell Charger & Balancer
Balancing resistor
Prevent backfeeding from other USB ports
LED will burn when battery wrong direction
USB C POWER

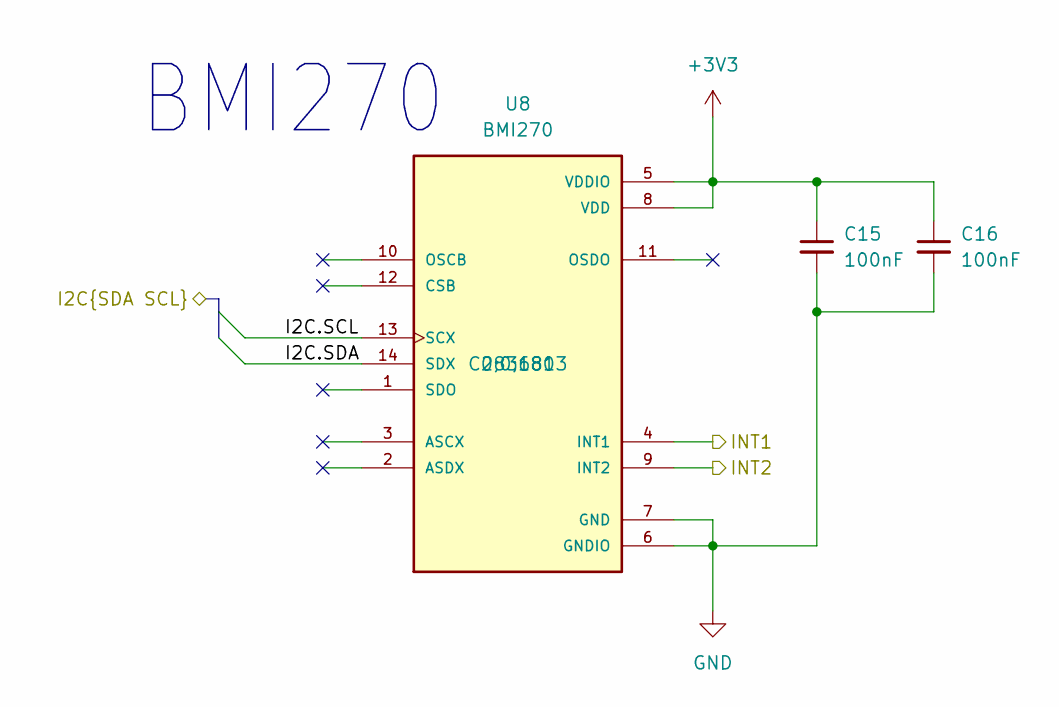
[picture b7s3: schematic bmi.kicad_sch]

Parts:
C15, C16: 100nF; C_0402_1005Metric; LCSC C307331
U8: BMI270; XDCR_BMI270; LCSC C2836813

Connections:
/I2C.SCL: U8.13 (SCX); also elsewhere on the board
/I2C.SDA: U8.14 (SDX); also elsewhere on the board
/INT1: U8.4 (INT1); also elsewhere on the board
/INT2: U8.9 (INT2); also elsewhere on the board

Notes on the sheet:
BMI270

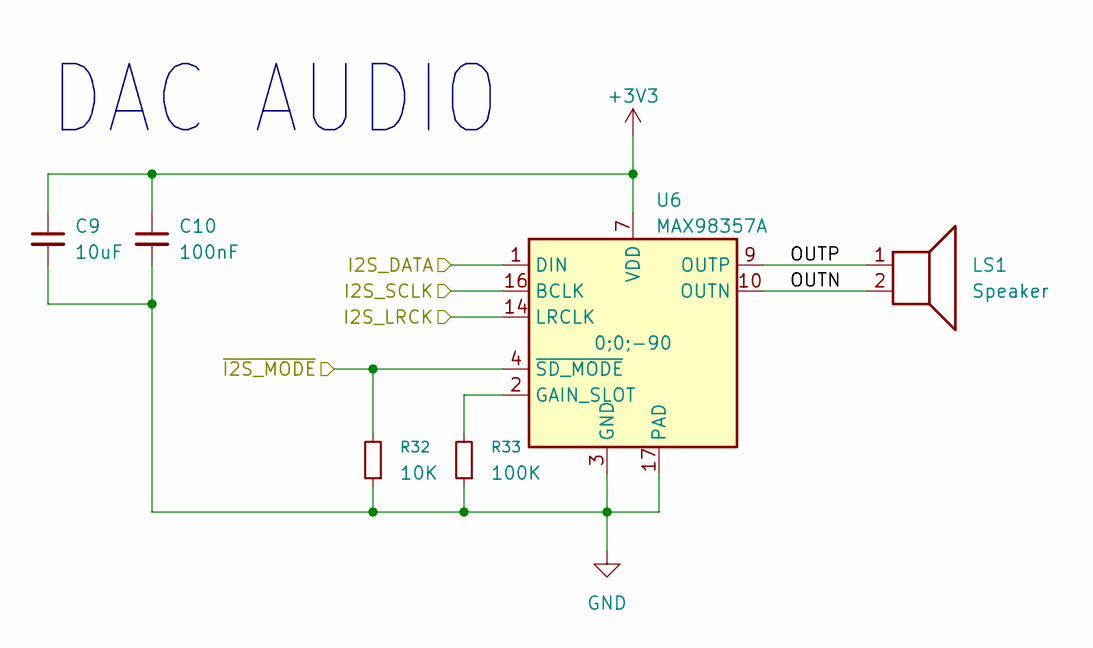
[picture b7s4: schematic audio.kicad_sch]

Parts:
C9: 10uF; C_0603_1608Metric; LCSC C96446
C10: 100nF; C_0402_1005Metric; LCSC C307331
LS1: Speaker; JST_SH_SM02B-SRSS-TB_1x02-1MP_P1.00mm_Horizontal; LCSC C160402
R32: 10K; R_0402_1005Metric; LCSC C25744
R33: 100K; R_0402_1005Metric; LCSC C25741
U6: MAX98357A; TQFN-16-1EP_3x3mm_P0.5mm_EP1.23x1.23mm; LCSC C910544

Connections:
/Audio/I2S_DATA: U6.1 (DIN); also elsewhere on the board
/Audio/I2S_LRCK: U6.14 (LRCLK); also elsewhere on the board
/Audio/I2S_SCLK: U6.16 (BCLK); also elsewhere on the board
/Audio/OUTN: LS1.2, U6.10 (OUTN)
/Audio/OUTP: LS1.1, U6.9 (OUTP)
/Audio/~I2S_MODE: R32.2, U6.4 (~SD_MODE); also elsewhere on the board
unnamed: R33.2, U6.2 (GAIN_SLOT)

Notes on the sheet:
DAC AUDIO
